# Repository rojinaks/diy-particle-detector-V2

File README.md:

# 🎛️ DIY Particle Detector v2.3

**Ein kompakter Teilchendetektor für Bildungs- und Outreach-Zwecke**, inspiriert vom DIY-particle-detector von Oliver Keller, weiterentwickelt am Physikalischen Institut der Universität Bonn.

---

### Dieses Repository enthält die Hardware- und Softwarebasis für einen DIY-Teilchendetektors

## ✨ Features

- SMD-basiertes PCB-Design  
- Python-Oszilloskop zur Signalvisualisierung 
- Dokumentierte Tests und Messergebnisse (Raumladungszone, Signal/noise Analyse)

---

## 📦 Inhalt

- `/hardware` → KiCad-Designs und Schaltpläne  
- `/codes` → Python-Auslesetool mit GUI, weitere messungen (Dioden Messung (Raumladungszone), Opamp vergleiche, Signal/noise Analyse)
- `/archives` → Weitere KiCad-Designs für vorherige Versionen  
- `/spice` → LTspice simulationen für verschiedene opamps

---

## Python Oszilloskop

```bash
  git clone https://github.com/rojinaks/diy-particle-detector-V2.git
  cd diy-particle-detector-V2/codes/auslese
  python oscilloscope.py

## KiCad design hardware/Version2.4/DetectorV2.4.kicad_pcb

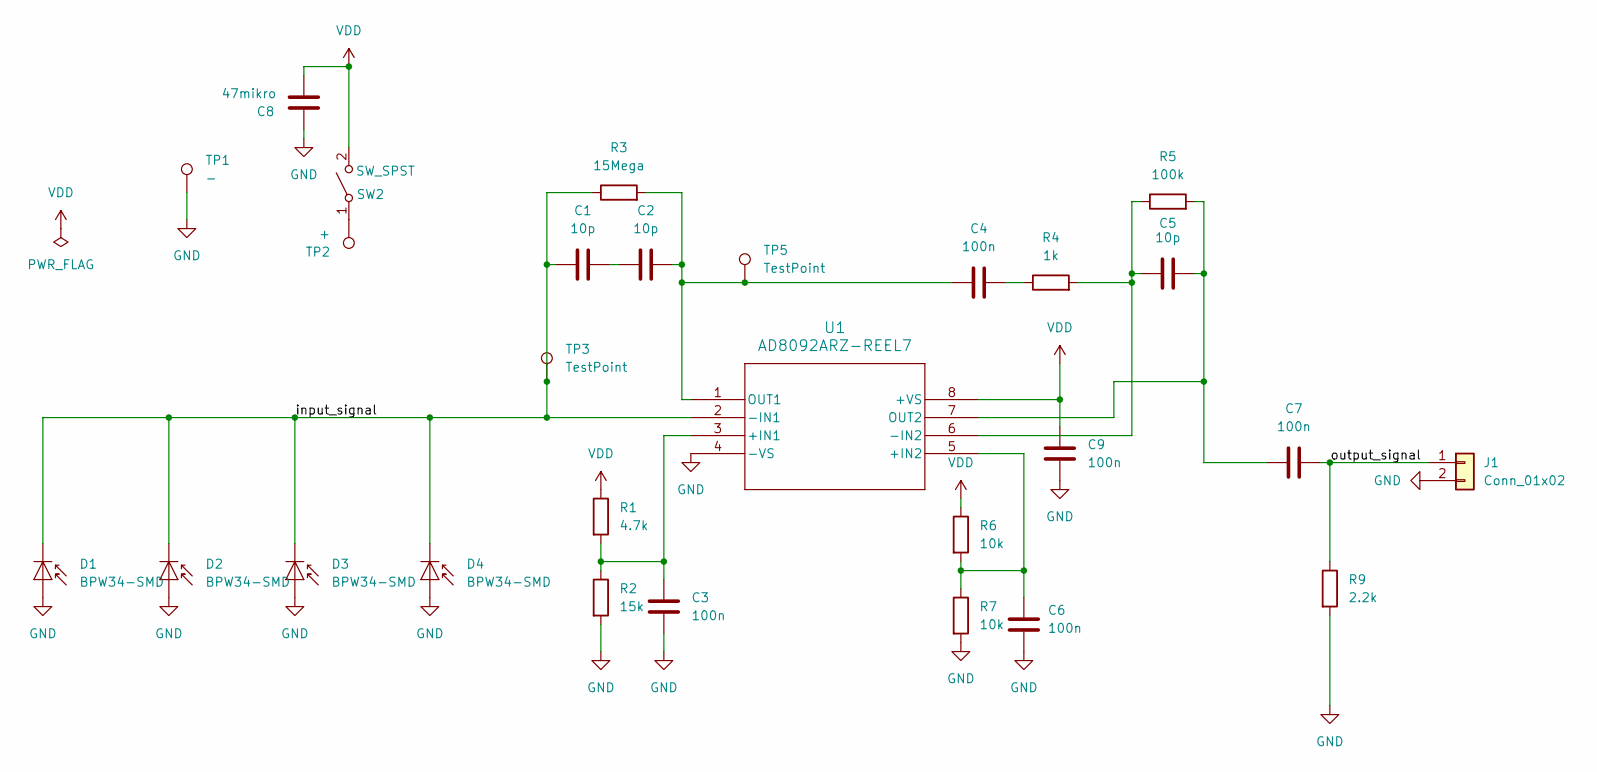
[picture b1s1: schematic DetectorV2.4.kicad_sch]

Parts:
C1, C2, C5: 10p; C_0805_2012Metric
C3, C4, C6, C7, C9: 100n; C_0805_2012Metric
C8: 47mikro; PCAP_EEHZ_D_PAN
D1, D2, D3, D4: BPW34-SMD; LED_VBPW34S_VIS
J1: Conn_01x02; CUI_SJ2-35813B-SMT-TR
R1: 4.7k; R_0805_2012Metric
R2: 15k; R_0805_2012Metric
R3: 15Mega; R_0805_2012Metric
R4: 1k; R_0805_2012Metric
R5: 100k; R_0805_2012Metric
R6, R7: 10k; R_0805_2012Metric
R9: 2.2k; R_0805_2012Metric
SW2: SW_SPST; SWITCH_102AGRLC
TP1: -; PinHeader_1x01_P2.54mm_Vertical
TP2: +; PinHeader_1x01_P2.54mm_Vertical
TP3, TP5: TestPoint; PinHeader_1x01_P2.54mm_Vertical
U1: AD8092ARZ-REEL7; R_8_ADI

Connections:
/input_signal: C1.1, D1.1 (K), D2.1 (K), D3.1 (K), D4.1 (K), R3.1, TP3.1, U1.2 (-IN1)
/output_signal: C7.2, J1.1, R9.1; also elsewhere on the board
GND: C3.2, C6.1, C8.2, C9.2, D1.2 (A), D2.2 (A), D3.2 (A), D4.2 (A), J1.2, R2.2, R7.2, R9.2, TP1.1, U1.4 (-VS); also elsewhere on the board
unnamed: C1.2, C2.1
unnamed: C4.2, R4.1
unnamed: SW2.1 (A), TP2.1
unnamed: C3.1, R1.2, R2.1, U1.3 (+IN1)
unnamed: C6.2, R6.2, R7.1, U1.5 (+IN2)
unnamed: C5.1, R4.2, R5.1, U1.6 (-IN2)
unnamed: C2.2, C4.1, R3.2, TP5.1, U1.1 (OUT1)
unnamed: C5.2, C7.1, R5.2, U1.7 (OUT2)
VDD: C8.1, C9.1, R1.1, R6.1, SW2.2 (B), U1.8 (+VS)

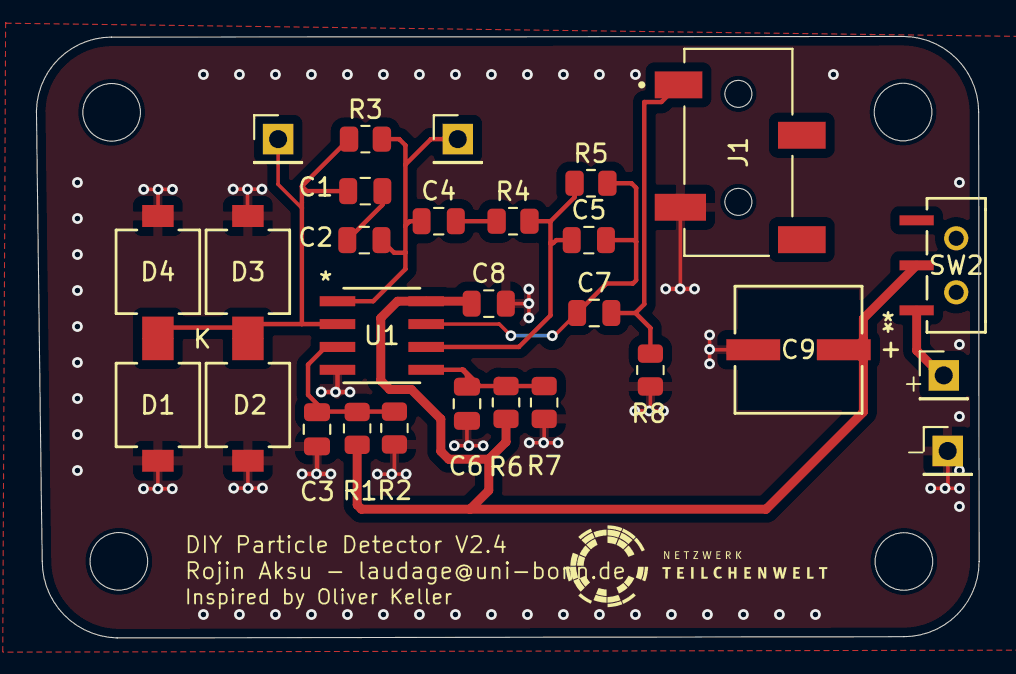
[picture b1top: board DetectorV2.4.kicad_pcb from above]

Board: 2 copper layers, 52.4 x 33.4 mm, 28 parts (0 on the bottom side), 12 nets.

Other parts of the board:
R8: 2.2k; R_0805_2012Metric

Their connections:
/output_signal: R8.1; also elsewhere on the board
GND: R8.2; also elsewhere on the board

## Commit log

2025-04-03 Initial KiCad commit
2025-04-03 Add .gitignore, README, and MIT license
2025-04-03 updated pdf without switch
2025-04-06 updated version - mit schalter + 47uF footprint
2025-04-06 updated pdf
2025-04-06 updated mit allen teilen aber fehlerhaft
2025-04-06 'spice' hinzugefügt
2025-04-06 LTspice-Datei detector_test1.asc
2025-04-06 änderung von paar werten aus simulation
2025-04-06 python cides
2025-04-06 python codes
2025-04-10 version 2.2
2025-04-10 mit version 2.2
2025-04-10 Bill of Materials
2025-04-11 version 2.3
2025-04-12 updated version 2.3
2025-04-12 Bill of materials 2.3
2025-04-12 updated mit logo und neuer schrift
2025-04-12 Moved DetectorV2.3 files to hardware folder
2025-04-12 alte versionen
2025-04-12 Clean up
2025-04-12 Add fp-info-cache to .gitignore
2025-04-12 updated 2.3 version
2025-04-12 Ignore future backup folders and zip files
2025-05-22 code test
2025-05-22 oszi test
2025-05-22 weitere tests
2025-05-22 oszi test 2
2025-05-23 oszi
2025-05-26 test
2025-06-03 signal/noise analyse
2025-06-03 messung
2025-06-06 dioden messung
2025-06-13 auswertung
2025-06-16 oszilloskop
2025-06-22 readme.md
2025-06-22 ignore Messungen_BA
2025-06-22 upadte
2025-06-24 version2.4
2025-08-12 messungen für V2.4
